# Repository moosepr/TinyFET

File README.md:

# TinyFET
Just an attiny85, and a FET

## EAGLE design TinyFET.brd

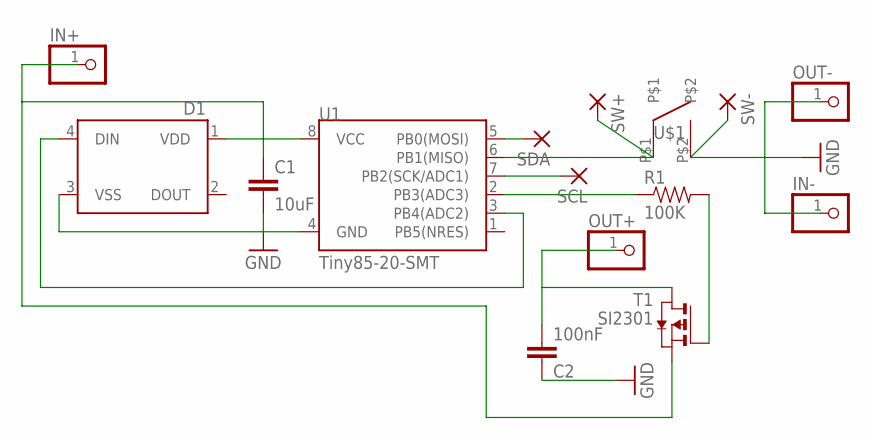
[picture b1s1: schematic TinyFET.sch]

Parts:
C1: 10uF; C0603K
C2: 100nF; C0603K
D1: WS2812B
IN+: PINHD-1X1; 1X01
IN-: PINHD-1X1; 1X01
OUT+: PINHD-1X1; 1X01
OUT-: PINHD-1X1; 1X01
R1: 100K; 0603-RES
SCL: SMD2; SMD1,27-2,54
SDA: SMD2; SMD1,27-2,54
SW+: SMD2; SMD1,27-2,54
SW-: SMD2; SMD1,27-2,54
T1: SI2301; SOT-23
U1: Tiny85-20-SMT; SO08-EIAJ
U$1: 5MMSNAP

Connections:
5V0@2: C2.2, OUT+.1, T1.1 (D)
GND: C1.2, C2.1, D1.3 (VSS), IN-.1, OUT-.1, SW-.1, U1.4 (GND), U$1.P$2
unnamed: SCL.1, U1.7 (PB2(SCK/ADC1))
unnamed: SDA.1, U1.5 (PB0(MOSI))
unnamed: R1.2, T1.3 (G)
unnamed: C1.1, D1.1 (VDD), IN+.1, T1.2 (S), U1.8 (VCC)
unnamed: D1.4 (DIN), U1.3 (PB4(ADC2))
unnamed: SW+.1, U1.6 (PB1(MISO)), U$1.P$1
unnamed: R1.1, U1.2 (PB3(ADC3))

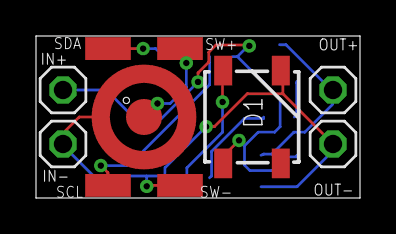
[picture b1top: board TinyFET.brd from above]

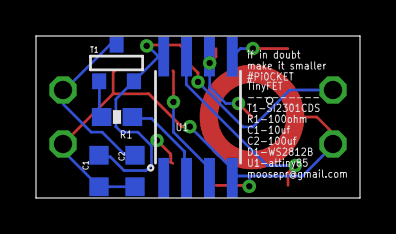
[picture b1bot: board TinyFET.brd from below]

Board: 2 copper layers, 18.0 x 9.0 mm, 15 parts (5 on the bottom side), 9 nets.

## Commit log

2017-09-19 Add files via upload
    added i2c functions maybe

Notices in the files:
parts and their libraries:
SparkFun-LED: Licensing: Creative Commons ShareAlike 4.0 International - https://creativecommons.org/licenses/by-sa/4.0
SparkFun-Passives: Licensing: CC v3.0 Share-Alike You are welcome to use this library for commercial purposes.
